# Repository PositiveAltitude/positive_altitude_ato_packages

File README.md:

# PositiveAltitude Atopile Packages

This repository is a library of reusable [Atopile](https://atopile.io/) hardware packages maintained by PositiveAltitude.

The focus is on practical, ready-to-integrate building blocks for embedded and power electronics designs. Packages in this repository are meant to be reused across projects rather than tied to a single board. The collection currently emphasizes:

- power-management building blocks
- battery-management frontends
- USB-C / USB-PD and power-path circuitry
- CAN interface parts
- small embedded support modules

All packages use explicit, LCSC-traceable component selections and are intended to build cleanly as standalone Atopile packages.

## Component inventory

See [`components_list.md`](components_list.md) for a categorized inventory of all LCSC-traceable parts used by the top-level package default BOMs.

That list intentionally excludes custom footprints and other non-purchasable items that do not appear in package BOM outputs.

## Current packages

### Embedded

- `packages/embedded/mcu/stm32g0b1kbu6_st`  
  STM32G0B1KBU6 MCU package with fixed power filtering and boot/reset support passives.

### Interface

#### CAN

- `packages/interface/can/mcp2518fdt_e_sl_microchip`  
  MCP2518FDT-E/SL 3.3 V SPI-to-CAN-FD controller with local clock and decoupling network.

- `packages/interface/can/tcan3413ddfr_ti`  
  TCAN3413DDFR 3.3 V CAN FD transceiver with local decoupling and exposed STB control.

#### Connector

- `packages/interface/connector/raspberry_pi_hat_socket_zhouri`  
  Raspberry Pi 40-pin HAT socket built around a footprint-compatible 2×20 2.54 mm through-hole female header.

### Power

#### Battery management

- `packages/power/battery_management/bq40z50rsmr_r2_4s_3a_ti`  
  BQ40Z50-R2-based 4S protected smart-battery frontend for up to 3 A continuous pack current, with internal balancing support, fixed no-thermistor biasing, SMBus telemetry, and BTP interrupt output.

#### Buck converters

- `packages/power/buck/tps56637rpar_5v1_5a_ti`  
  Fixed 5.1 V, 5 A buck converter package based on TI TPS56637RPAR, aimed at Raspberry Pi-class loads.

- `packages/power/buck/tps62933drlr_3v3_ti`  
  Fixed 3.3 V buck converter package based on TI TPS62933DRLR.

#### Charger

- `packages/power/charger/bq25756rrvr_4s_2a_ti`  
  BQ25756-based 4S Li-ion buck-boost charger package with 1 A default hardware charge limit, 20 V max input, I2C control, and compact XNRUSEMI dual-MOSFETs.

#### Power mux

- `packages/power/power_mux/tps2121ruxr_20v_4a_ti`  
  Minimal generic 20 V-class priority power mux around TI TPS2121RUXR with reverse-current blocking and exported status.

#### USB Power Delivery

- `packages/power/usb_pd/tps25730drefr_20v_3a_ti`  
  Autonomous sink-only USB-PD controller block around TI TPS25730DREFR with a 20 V / 3 A target contract, 5 V fallback, and optional exposed digital sideband signals.

## Maintainer

PositiveAltitude  
<dima@positivealtitude.dev>

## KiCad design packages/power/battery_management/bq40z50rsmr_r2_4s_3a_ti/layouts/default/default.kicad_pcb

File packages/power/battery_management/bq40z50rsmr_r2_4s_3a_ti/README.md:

# bq40z50rsmr_r2_4s_3a_ti

Reusable Atopile package for a **4S BQ40Z50-R2 smart-battery frontend**.

## Exposed interface

- `pack` protected pack power interface
- `raw_battery` raw cell-stack power interface upstream of the protection FETs for an external battery connector or harness
- `i2c` SMBus interface
- `btp_int` battery-trip-point interrupt output

## Included

- TI `BQ40Z50RSMR-R2` (`LCSC C2845123`)
- Two TI `CSD18543Q3A` N-FETs (`LCSC C840100`) for the protected high-side back-to-back path, matching the charger package MOSFET
- Internal cell-tap filtering and balancing support wiring
- 100-Ω series resistors on SMBC/SMBD and VC sense lines per the TI reference schematic
- Unused TS1-TS4 and `nDISP` pinned to `VSS`
- Murata `PRF15BB103RB6RC` (`LCSC C443668`) 0402 safety PTC thermistor at the FETs

## Intentionally omitted

- MCU / firmware logic
- SMBus pull-ups
- external pack/cell thermistors
- secondary protection / chemical fuse
- LED / button / pack-presence UX features
- dedicated `PCHG` path in this revision

## Important integration note

This package captures the hardware frontend only. Correct chemistry, balancing policy,
temperature behavior, and any permanent-fail masking still depend on proper
`BQ40Z50-R2` data-flash configuration in TI tooling.

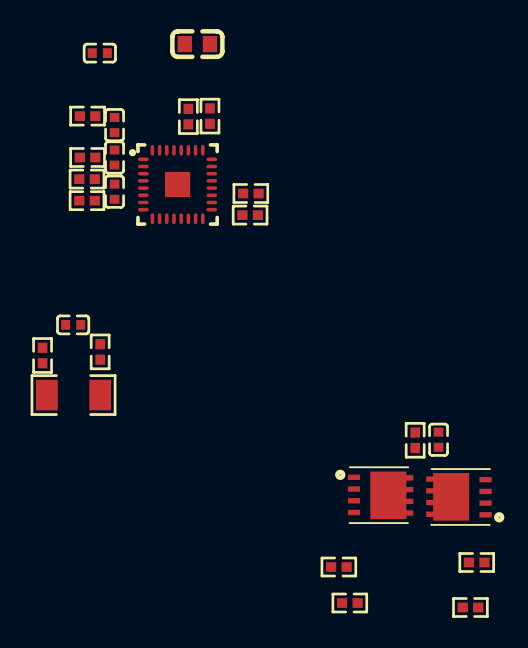
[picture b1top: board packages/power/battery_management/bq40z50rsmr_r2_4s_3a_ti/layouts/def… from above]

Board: 2 copper layers, 26 parts (0 on the bottom side), 21 nets, no tracks yet.

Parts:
C1, C2, C4, C5, C6, C7: C0402
C8: C0603
Q1, Q2: VSONP-8_L3.1-W3.1-P0.65-LS3.5-BL
R1, R2, R3, R4, R5, R6, R8, R9, R10, R11, R12, R13, R14, R15, R18: R0402
R7: R1206
U1: VQFN-32_L4.0-W4.0-P0.40-TL-EP1.4_2

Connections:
1: C1.1, R5.1, U1.23
1-1: C8.1, U1.1
CHG: R2.1, U1.31
D: Q1.5, Q1.6, Q1.7, Q1.8, Q1.9, Q2.5, Q2.6, Q2.7, Q2.8, Q2.9
DSG: R4.1, U1.28
G: Q1.4, R1.1, R2.2
G-1: Q2.4, R3.1, R4.2
SMBC: R14.2, U1.19
SMBD: R15.2, U1.18
hv: Q1.1, Q1.2, Q1.3, R1.2, R6.1
lv: R7.2, R9.1
pack_filtered: R6.2, U1.27
raw_battery-hv: C1.2, Q2.1, Q2.2, Q2.3, R3.2, R5.2, R13.1, R18.1, U1.24, U1.32
raw_battery-lv: C4.2, C8.2, R7.1, R8.1, U1.9, U1.10, U1.11, U1.12, U1.13, U1.16, U1.17, U1.25, U1.33
srn_filtered: C2.2, R8.2, U1.6
srp_filtered: C2.1, R9.2, U1.8
vc1_filtered: C4.1, C5.2, R10.2, U1.5
vc2_filtered: C5.1, C6.2, R11.2, U1.4
vc3_filtered: C6.1, C7.2, R12.2, U1.3
vc4_filtered: C7.1, R13.2, U1.2
vcc_filtered: R18.2, U1.26

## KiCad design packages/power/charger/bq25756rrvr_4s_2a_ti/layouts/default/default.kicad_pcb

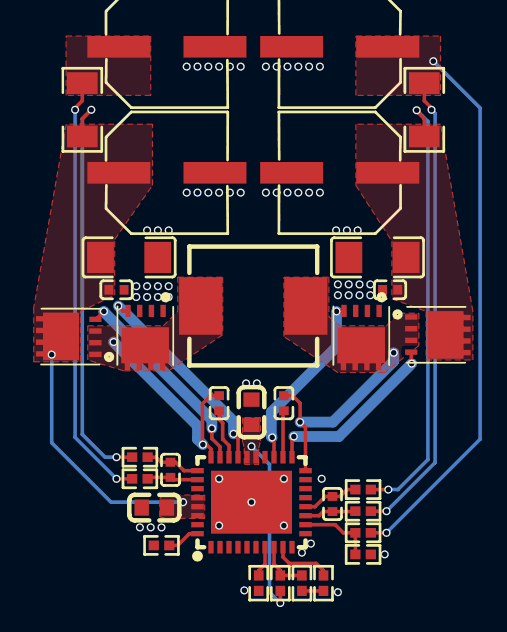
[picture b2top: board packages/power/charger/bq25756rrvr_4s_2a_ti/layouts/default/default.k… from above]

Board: 4 copper layers, 33 parts (0 on the bottom side), 23 nets.

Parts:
C1, C7, C8, C9, C11, C13: C0402
C2, C3, C4, C5: CAP-SMD_BD6.3-L6.6-W6.6-FD
C10, C12: C1206
C15, C16: C0603
L1: IND-SMD_L7.1-W6.6_SLO0650H
Q1, Q2, Q3, Q4: VSONP-8_L3.1-W3.1-P0.65-LS3.5-BL
R1, R6: R1206
R2, R3, R4, R5, R7, R8, R9, R10, R13, R14, R15: R0402
U1: TQFN-36_L6.0-W5.0-P0.50-BL-EP-1

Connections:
1: C4.1, C12.1, C13.1, C16.1, Q3.5, Q3.6, Q3.7, Q3.8, Q3.9, R4.1, R6.2, U1.32, U1.33, U1.34
1-1: C2.1, C10.1, C11.1, Q1.5, Q1.6, Q1.7, Q1.8, Q1.9, R1.1, R8.1
1-2: C8.1, U1.26
1-3: C8.2, L1.1, Q3.1, Q3.2, Q3.3, Q4.5, Q4.6, Q4.7, Q4.8, Q4.9, U1.28
1-4: C9.1, U1.20
1-5: C15.2, R15.1, U1.23, U1.24
2: C9.2, L1.2, Q1.1, Q1.2, Q1.3, Q2.5, Q2.6, Q2.7, Q2.8, Q2.9, U1.18
FB: R9.1, R10.2, U1.12
FSW_SYNC: R13.1, U1.36
G: Q1.4, U1.19
G-1: Q2.4, U1.21
G-2: Q3.4, U1.27
G-3: Q4.4, U1.25
ICHG: R2.1, U1.9
TS: R14.1, R15.2, U1.8
acn_filtered: C1.2, R4.2, U1.29
acp_filtered: C1.1, R5.2, U1.30
battery-hv: C3.1, R1.2, R7.1, R10.1
hv: C5.1, R5.1, R6.1
lv: C2.2, C3.2, C4.2, C5.2, C10.2, C11.2, C12.2, C13.2, C15.1, C16.2, Q2.1, Q2.2, Q2.3, Q4.1, Q4.2, Q4.3, R2.2, R3.2, R9.2, R13.2, R14.2, U1.10, U1.11, U1.17, U1.22, U1.35, U1.37
nCE: R3.1, U1.7
srn_filtered: C7.2, R7.2, U1.13
srp_filtered: C7.1, R8.2, U1.14

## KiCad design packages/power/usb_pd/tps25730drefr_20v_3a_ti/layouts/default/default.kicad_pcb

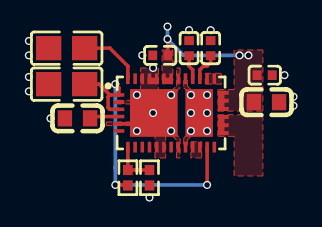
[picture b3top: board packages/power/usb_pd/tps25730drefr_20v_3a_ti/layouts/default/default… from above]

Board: 4 copper layers, 11 parts (0 on the bottom side), 10 nets.

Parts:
C1, C2, C6, C8: C0402
C3, C7: C0603
C4, C5: C0805
R3, R4: R0402
U1: QFN-38_L6.0-W4.0-P0.40-TL-EP_RJK

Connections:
1: R3.1, R4.2, U1.7
DRAIN: U1.15, U1.30, U1.40
adc_limit_top-1: C4.1, R4.1, U1.1, U1.3, U1.18
cc1-1: C1.1, U1.28
cc2-1: C2.1, U1.29
controller-1: C3.1, U1.4
hv: C5.1, U1.38
lv: C1.2, C2.2, C3.2, C4.2, C5.2, C6.2, C7.2, C8.2, R3.2, U1.2, U1.5, U1.11, U1.12, U1.14, U1.16, U1.17, U1.26, U1.27, U1.31, U1.34, U1.35, U1.36, U1.39
sink_vbus-hv: U1.20, U1.21, U1.22
usb_vbus-hv: C6.1, C7.1, C8.1, U1.23, U1.24, U1.25, U1.32, U1.33

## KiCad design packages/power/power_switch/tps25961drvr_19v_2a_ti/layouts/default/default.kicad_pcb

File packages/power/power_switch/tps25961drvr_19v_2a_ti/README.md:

# tps25961drvr_19v_2a_ti

Protected high-side power-switch package based on TI `TPS25961DRVR`.

## What it includes

- TI `TPS25961DRVR` eFuse / power switch (`LCSC C5571272`)
- fixed 2 A current-limit resistor
- fixed OVLO divider for up to 19 V input rails
- 100 nF input capacitor
- 1 uF output capacitor

## Interface

- `power_in` — input power rail
- `power_out` — protected output rail
- `enable` — active-high logic control

## Behavior

- intended for 2.7 V to 19 V input rails
- current limit is set to about 2 A
- OVLO is set so normal 4S battery voltages pass while higher faults are blocked
- startup slew rate / soft-start is handled internally by the IC

## Notes

- `enable` is referenced to input ground
- drive `enable` from normal 3.3 V push-pull logic
- do not leave `enable` / EN floating

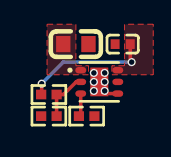
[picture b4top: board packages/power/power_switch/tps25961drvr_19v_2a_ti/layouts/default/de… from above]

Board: 2 copper layers, 6 parts (0 on the bottom side), 5 nets.

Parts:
C1: C0402
C2: C0603
R1, R2, R3: R0402
U1: WSON-6_L2.0-W2.0-P0.65-TL-EP

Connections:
2: R2.1, R3.2, U1.2
ILIM: R1.1, U1.3
hv: C2.1, U1.1
lv: C1.2, C2.2, R1.2, R2.2, U1.4, U1.7
power_in-hv: C1.1, R3.1, U1.6

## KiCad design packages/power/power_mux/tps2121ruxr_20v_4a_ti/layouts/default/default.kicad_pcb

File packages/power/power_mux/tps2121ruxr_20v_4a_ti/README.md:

# tps2121ruxr_20v_4a_ti

Short two-input power mux package based on TI `TPS2121RUXR`.

## What it includes

- TI `TPS2121RUXR` power mux (`LCSC C485916`)
- local 100 nF bypass capacitors on both inputs and the output
- internal resistor network for priority selection
- internal current-limit resistor
- soft-start capacitor

## Interface

- `high_priority` — preferred input source
- `low_priority` — fallback input source
- `out` — muxed output
- `status` — raw status output from the TPS2121

## Behavior

- `high_priority` maps to IN1
- `low_priority` maps to IN2
- valid `high_priority` input is preferred over `low_priority`
- package is intended for up to 20 V inputs and up to 4 A output current

## Notes

- overvoltage comparators are disabled internally
- this package does not include upstream protection or downstream bulk capacitance

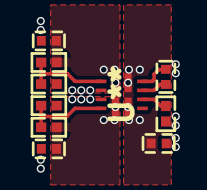
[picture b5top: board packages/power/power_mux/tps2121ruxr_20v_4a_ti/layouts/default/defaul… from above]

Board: 4 copper layers, 10 parts (0 on the bottom side), 8 nets.

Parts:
C2, C4, C6, C7: C0402
R1, R2, R3, R4, R5: R0402
U**: TPS2121RUXR

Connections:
1: R2.1, R3.2, U**.3
1-1: R4.1, R5.2, U**.6
ILM: R1.1, U**.10
SS: C7.1, U**.11
high_priority-hv: C2.1, R5.1, U**.7
hv: C4.1, R3.1, U**.2
lv: C2.2, C4.2, C6.2, C7.2, R1.2, R2.2, R4.2, U**.4, U**.5, U**.12
out-hv: C6.1, U**.1, U**.8

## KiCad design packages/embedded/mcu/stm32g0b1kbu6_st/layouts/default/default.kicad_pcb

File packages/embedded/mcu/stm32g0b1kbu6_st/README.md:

# stm32g0b1kbu6_st

Basic STM32G0B1KBU6 MCU package with the minimum support parts.

## What it includes

- ST `STM32G0B1KBU6` MCU (`LCSC C5159549`)
- local 4.7 uF bulk capacitor
- local 100 nF bypass capacitor
- 10 kΩ BOOT0 pulldown
- 100 nF reset capacitor on `NRST`

## Interface

- `power` supply input
- MCU GPIOs exported as signals
- reset and boot pins exposed through the package signals

## Notes

- intended as a simple reusable MCU core
- does not include clocks, connectors, debug header, or external peripherals
- supply range is constrained to 1.7 V to 3.6 V in the package

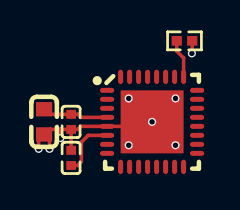
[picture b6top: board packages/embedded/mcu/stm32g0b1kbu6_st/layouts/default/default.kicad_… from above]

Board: 2 copper layers, 5 parts (0 on the bottom side), 4 nets.

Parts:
C1, C3: C0402
C2: C0603
R1: R0402
U1: QFN-32_L5.0-W5.0-P0.50-TL-EP3.5

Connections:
PA14_BOOT0: R1.1, U1.25
PF2_NRST: C1.1, U1.6
hv: C2.1, C3.1, U1.4
lv: C1.2, C2.2, C3.2, R1.2, U1.5, U1.33

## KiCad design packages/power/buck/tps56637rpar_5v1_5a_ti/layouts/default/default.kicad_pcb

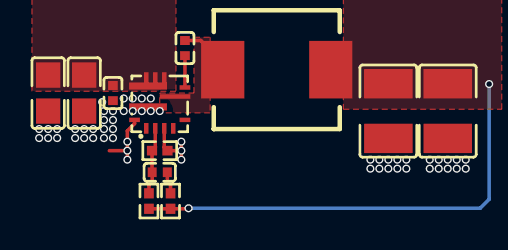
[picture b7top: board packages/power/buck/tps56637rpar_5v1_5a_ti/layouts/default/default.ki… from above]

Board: 4 copper layers, 12 parts (0 on the bottom side), 7 nets.

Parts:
C1, C4, C7: C0402
C2, C3: C0805
C5, C6: C1210
L1: IND-SMD_L7.0-W6.6
R1, R2, R3: R0402
U1: VQFN-HR-10_L3.0-W3.0_RPA

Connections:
1: C7.1, R3.2
2: C7.2, R1.1, R2.2, U1.2
BOOT: C1.1, U1.7
SW: C1.2, L1.1, U1.6
hv: C2.1, C3.1, C4.1, U1.8
lv: C2.2, C3.2, C4.2, C5.2, C6.2, R1.2, U1.3, U1.9, U1.10
power_out-hv: C5.1, C6.1, L1.2, R2.1, R3.1

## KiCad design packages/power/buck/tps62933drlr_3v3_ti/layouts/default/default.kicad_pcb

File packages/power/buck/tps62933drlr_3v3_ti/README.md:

# tps62933drlr_3v3_ti

Compact 3.3 V buck-converter package based on TI `TPS62933DRLR`.

## What it includes

- TI `TPS62933DRLR` buck regulator (`LCSC C3200405`)
- 2x 10 uF input capacitors
- 2x 22 uF output capacitors
- 100 nF input, bootstrap, soft-start, and output bypass capacitors
- 2.2 uH power inductor
- feedback divider for 3.3 V output
- EN divider that enables the converter at approximately 10 V input

## Interface

- `power_in` — input supply
- `power_out` — regulated 3.3 V output

## Behavior

- output is fixed to 3.3 V
- package target is limited to 1 A output current
- `RT` is tied to GND for fixed 1.2 MHz operation
- `EN` is not tied directly to VIN; the divider delays startup until VIN is about 10 V

## Notes

- this package is intended for higher-input-voltage rails where 3.3 V is needed locally
- it uses explicit local parts to keep BOM selection deterministic
- TI's TPS62933 datasheet says not to allow `VOUT` to exceed `VIN`; if your system can hold the 3.3 V rail up after input power falls away, add an external diode or equivalent protection path so `power_out` cannot rise above `power_in`

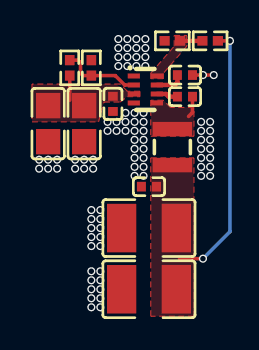
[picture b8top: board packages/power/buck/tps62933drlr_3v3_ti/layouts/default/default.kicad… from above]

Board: 4 copper layers, 14 parts (0 on the bottom side), 8 nets.

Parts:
C1, C4, C7, C8: C0402
C2, C3: C0805
C5, C6: C1210
L1: IND-SMD_L2.5-W2.0_MHCHL2520
R1, R2, R3, R4: R0402
U1: SOT-583-8_L2.1-W1.2-P0.50-LS1.6-BR

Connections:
2: R3.1, R4.2, U1.2
BST: C1.1, U1.6
FB: R1.1, R2.2, U1.8
SS: C7.1, U1.7
SW: C1.2, L1.1, U1.5
hv: C2.1, C3.1, C4.1, R4.1, U1.3
lv: C2.2, C3.2, C4.2, C5.2, C6.2, C7.2, C8.2, R1.2, R3.2, U1.1, U1.4
power_out-hv: C5.1, C6.1, C8.1, L1.2, R2.1

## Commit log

2026-04-02 Restructure repo into package collection
2026-04-02 Add first MLCC package
2026-04-02 Add Samsung MLCC package
2026-04-02 Add 0402 resistor packages
2026-04-02 Rename AGENTS to AGENTS.md
2026-04-02 Cleanup
2026-04-03 Add TPS62933 3V3 buck package
2026-04-03 Update TPS62933 buck package
2026-04-04 Update TPS62933 buck passives and prune parts
2026-04-04 Update TPS62933
2026-04-04 Add STM32G0B1KBU6 MCU package
2026-04-04 Add TCAN3413DDFR CAN transceiver package
2026-04-04 Add MCP2518FD SPI to CAN controller package
2026-04-05 Add TPS56637 package
2026-04-05 Update AGENTS component selection guidance
2026-04-05 Add Raspberry Pi HAT connector package
2026-04-06 Add BQ25756 4S charger package
2026-04-06 Switch BQ25756 charger to Vishay dual MOSFETs
2026-04-06 Switch BQ25756 charger to XRS30V06D
2026-04-08 Add BQ76907 4S battery management package
2026-04-09 Update gitignore
2026-04-09 BQ40Z50RSMR 4S frontend
2026-04-10 Preserve a lean USB-PD sink package with honest current straps
    Package the TPS25730 sink block while removing stale local part libraries left behind after changing the ADC current straps from a fixed 3 A/3 A setting to a 0 A/3 A window. Keep only the local parts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
    Constraint: Repository packages must keep explicit LCSC-backed parts and verify with ato
    Constraint: build/ and .ato/ artifacts are ignored, so the commit must rely on source, layouts, and package-local parts only
    Rejected: Leave stale YAGEO local part libraries in the package | bloats the package and leaves dead
2026-04-10 Keep the power mux package free of misleading local-part artifacts
    Reviewing the TPS2121 power mux package found that its local part set is still fully referenced, so there were no dead part libraries to delete. The concrete cleanup was to fix the 39 kΩ resistor foo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
    Constraint: Repository packages must keep explicit LCSC-backed local parts and verify with ato before completion
    Constraint: build/ and .ato/ artifacts are ignored, so only package source, layouts, and local parts can be committed
    Rejected: Delete the 39 kΩ local part library as
2026-04-11 Align the USB-PD sink front end with the TPS25730 reference design
    Update the TPS25730DREFR package so the receptacle-facing VBUS capacitance matches TI's recommended CVBUS window while the switched PPHV side carries the larger bulk energy store recommended for the 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
    Constraint: USB-facing sink capacitance should stay inside the stricter Type-C-facing VBUS guidance while the TPS25730D still needs its recommended board capacitances
    Constraint: Repository packages must keep explicit LCSC-backed parts and verify with ato
    Rejected: Keep 22 uF directly on usb_vbus | ex
2026-04-12 Wip TPS25730
2026-04-12 TPS25730 update
2026-04-12 Keep the USB-PD sink package deterministic and schematic-friendly
    The package now uses explicit local passive part modules again, drops the
    unnecessary package-level sink output capacitor, and forces readable net
    names for the exposed rails and key internal strap nets. The resulting
    layout outputs stay aligned with the package contract while avoiding the
    opaque auto-generated net labels that made the schematic harder to use.
    Constraint: Package must build with the current atopile CLI in this repo
2026-04-12 Keep package names stable while moving the repo onto the current Atopile release
    The package catalog now uses current Atopile metadata and drops LCSC
    codes from package names so external users see cleaner, more stable
    paths. The README was rewritten around the renamed package set, and the
    obsolete BQ76907 battery-management package was removed from the
    repository.
    Constraint: Package names should not expose supplier-specific LCSC suffixes
2026-04-12 Make package builds deterministic by wiring explicit local parts
    The remaining packages now reference package-local concrete passives,
    inductors, and other small parts directly instead of relying on generic
    part-picker resolution. This aligns the source with the local
    assets and removes the flaky live EasyEDA lookup path that was blocking
    verification.
    Constraint: Builds must not depend on unstable live part-picking when local package assets already exist
2026-04-12 Make package schematics more readable and align passive choices with repo guidance
    This pass improves the human-facing quality of the package library.
    Explicit local capacitor/resistor parts now carry short descriptive
    comments at the point of use, the MCP2518FD package swaps its 1uF bulk
    capacitor to a 0603 part to match the current sizing rule, and several
    packages add better net-name overrides for exposed and important internal
    signals.
2026-04-13 Expose raw battery connections without forcing net overrides
    The battery frontend no longer assigns override_net_name values, and it now
    exports raw_battery alongside the protected pack so downstream designs can add
    a connector or harness wiring at the package boundary. I also removed the
    repository guidance that encouraged override-based naming and rebuilt the
    checked-in layouts so their net metadata matches the source after the change.
    Constraint: Package instances were breaking when internal net overrides propagated into downstream designs
2026-04-13 Finish removing net-name overrides from reusable packages
    This completes the package-level override cleanup by deleting the remaining
    `override_net_name` assignments from the library's reusable package modules and
    rebuilding their checked-in layouts so generated net metadata matches source.
    The package interfaces stay the same; only the forced net naming was removed so
    these modules compose cleanly when imported into downstream designs.
    Constraint: The library must stay reusable and avoid imposed internal net names leaking into consuming designs
2026-04-14 Align the BQ40Z50 frontend with TI's recommended sense filtering
    The cell-tap, SMBus, unused-pin, and PTC wiring had drifted from the TI
    reference guidance. This updates the package so VC filtering happens on the
    IC side of the 100 Ω resistors, unused TS/DISP pins are grounded, SMBus gets
    series damping, unnecessary bypass caps are removed, and the PTC safety path
    uses a concrete 0402 Murata part.
    Constraint: Must keep the package reusable, deterministic, and sourced from LCSC parts already compatible with Atopile
2026-04-14 Reduce BQ25756 feedback divider footprint without changing regulation
    The charger package used a 0603 249 kΩ / 0.1% FB-top resistor even though the
    node's dissipation and voltage stress allow a 0402 part. This swaps in a
    concrete 0402 Viking Tech resistor with the same nominal value and tolerance so
    layout stays tighter without changing the programmed charge voltage.
    Constraint: Keep the exact 249 kΩ / 0.1% feedback ratio to preserve standalone charge-voltage programming
    Constraint: Must use an LCSC-sourced deterministic part compatible with local Atopile assets
2026-04-14 Filter the BQ40Z50 PTC input against switching noise
    The new FET safety PTC path benefits from a local filter capacitor so the gauge
    sees a cleaner temperature-protection signal instead of raw switching noise from
    the pack side. This adds the requested 100 nF capacitor from PTC to BAT using
    an existing package-local Murata MLCC.
    Constraint: Must preserve the existing deterministic package-local part set where possible
    Constraint: Verification must be done with ato in the changed package directory
2026-04-14 Add a minimal TI 5 V to 3.3 V LDO building block
    The library lacked a tiny linear-regulator package for simple housekeeping rails.
    This adds a reusable TLV70033DDCR package with the minimum external BOM from the
    TI application circuit: the regulator plus one input and one output capacitor.
    EN is hard-tied high so downstream designs can drop it in without extra logic.
    Constraint: Must use an LCSC-stocked part from a reputable vendor and keep the package deterministic with local assets
    Constraint: User requested a low-BOM solution, so the implementation must stay at LDO + 2 caps
2026-04-14 Add a dual-rail current-limited power switch building block
    The library needed a reusable protected high-side switch that can serve both
    3.3 V rails and 4S battery-class rails while still being controllable from
    ordinary 3.3 V push-pull logic. This adds a TPS25961 package with fixed 2 A
    current limiting, fixed OVLO suitable for 4S operation, and the IC's native
    slew-rate-controlled startup.
    Constraint: Must support both 3.3 V and 4S rails with one package while staying inside the selected IC's 19 V operating limit
2026-04-14 Preserve the PositiveAltitude SWD footprint geometry in-package
    The first import of the PositiveAltitude SWD connector simplified the probe pads
    too aggressively and no longer matched the source design intent. This revision
    keeps the original contact geometry by vendoring the footprint and encoding the
    custom pad outline in a form that the local Atopile/KiCad toolchain can still
    parse and rebuild.
    Constraint: The package must stay faithful to the source repository's footprint geometry rather than substituting generic pads
2026-04-15 Keep package outputs aligned with production BOMs and documented parts
    This removes top-level package example targets and their checked-in example
    layouts so the library tracks the maintained default package outputs only.
    It also adds minimal KiCad project files for each default layout and a
    root components inventory derived from the top-level default BOMs, then
    links that inventory from the repository guidance and README so future
    part changes have one canonical summary.
2026-04-16 22uF cap update, TPS56637 update
2026-04-17 TPS56637 layout
2026-04-17 Add Raspberry Pi HAT layout
2026-04-17 Reduce redundant package APIs by dropping empty alias wrappers
    Several packages carried secondary modules whose only behavior was
    `pass` inheritance from the real package module. Removing those wrappers
    keeps each package anchored on a single canonical entry module and
    reduces duplicate names without changing the underlying circuit logic.
    The one build target that still pointed at an alias now targets the
    primary module directly.
2026-04-17 TCAN3414 update
2026-04-17 RP hat update
2026-04-17 SWD connector update
2026-04-17 RP hat readme
2026-04-19 MCP2518 update
2026-04-19 TLV70033 update
2026-04-19 TPS62933 update
2026-04-19 TPS56637 update
2026-04-19 STM32G0 update
2026-04-20 TPS2121 layout
2026-04-20 Uncommited parts
2026-04-20 TPS25961 layout
2026-04-20 tps62933 readme
2026-05-15 tps25730 layout
2026-05-28 Charger layout wip
2026-06-13 charger layout
